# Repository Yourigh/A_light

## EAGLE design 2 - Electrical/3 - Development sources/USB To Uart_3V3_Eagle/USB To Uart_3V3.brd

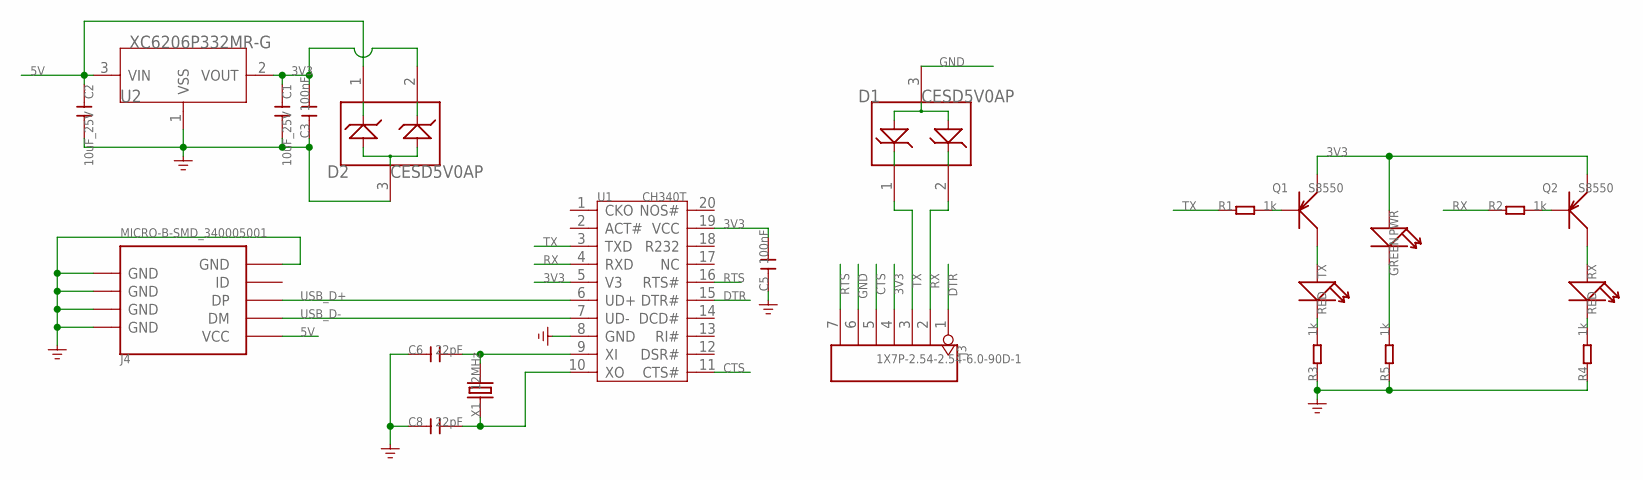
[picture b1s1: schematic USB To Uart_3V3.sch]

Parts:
C1, C2: 10uF_25V; C0805
C3, C5: 100nF; C0402
C6, C8: 22pF; C0402
D1, D2: CESD5V0AP; SOT23
J3: 1X7P-2.54-2.54-6.0-90D-1; 7P-2.54-65/35MIL
J4: MICRO-B-SMD_340005001; MICRO-USB
PWR: GREEN; LED-0603
Q1, Q2: S8550; SOT23
R1, R2, R3, R4, R5: 1k; R0402
RX: RED; LED-0603
TX: RED; LED-0603
U1: CH340T; SSOP20
U2: XC6206P332MR-G; SOT23
X1: 12MHz; HC49UP

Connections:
3V3: C1.1, C3.2, C5.2, D2.2, J3.4, PWR.+, Q1.2 (E), Q2.2 (E), U1.5 (V3), U1.19 (VCC), U2.2 (VOUT)
5V: C2.1, D2.1, J4.1 (VCC), U2.3 (VIN)
CTS: J3.5, U1.11 (CTS#)
DTR: J3.1, U1.15 (DTR#)
GND: C1.2, C2.2, C3.1, C5.1, C6.1, C8.1, D1.3, D2.3, J3.6, J4.5 (GND), J4.S1 (GND), J4.S2 (GND), J4.S3 (GND), J4.S4 (GND), J4.S5 (GND), J4.S6 (GND), R3.1, R4.1, R5.1, U1.8 (GND), U2.1 (VSS)
unnamed: Q1.3 (C), TX.+
unnamed: Q2.3 (C), RX.+
unnamed: C6.2, U1.9 (XI), X1.2
unnamed: C8.2, U1.10 (XO), X1.1
unnamed: R3.2, TX.-
unnamed: Q1.1 (B), R1.2
unnamed: Q2.1 (B), R2.2
unnamed: R4.2, RX.-
unnamed: PWR.-, R5.2
RTS: J3.7, U1.16 (RTS#)
RX: D1.2, J3.2, R2.1, U1.4 (RXD)
TX: D1.1, J3.3, R1.1, U1.3 (TXD)
USB_D+: J4.3 (DP), U1.6 (UD+)
USB_D-: J4.2 (DM), U1.7 (UD-)

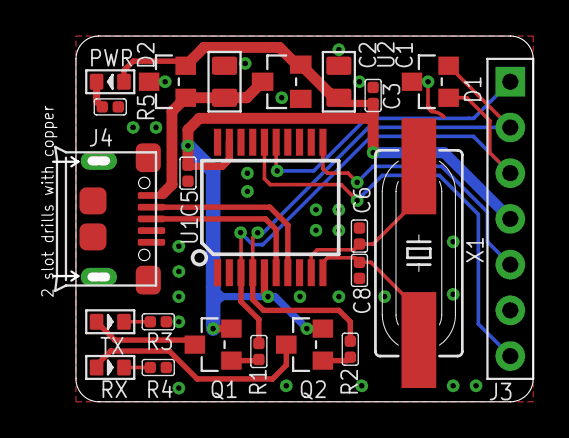
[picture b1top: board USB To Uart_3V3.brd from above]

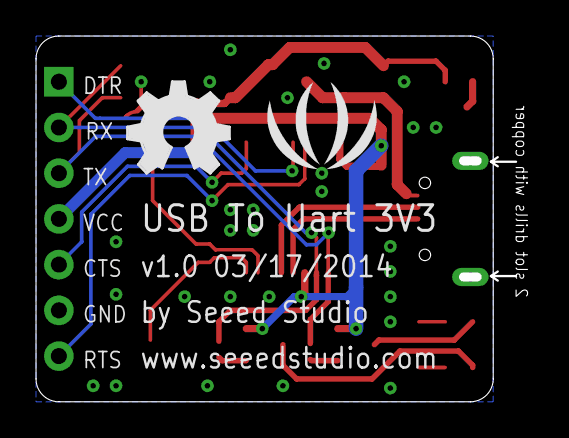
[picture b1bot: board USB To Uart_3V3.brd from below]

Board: 2 copper layers, 26.7 x 20.3 mm, 25 parts (2 on the bottom side), 19 nets.

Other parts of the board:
U$8: LOGO_SILK
U$9: OSHW_FILLX200_NOTEXT

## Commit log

2020-11-07 add code
2020-11-07 MQTT connected
    connected to broker, broker reported
    1604775397: New client connected from 192.168.1.8 as A-light (p2, c1, k15, u'homeassistant').
    1604775420: Client A-light has exceeded timeout, disconnecting.
2020-11-07 MQTT identified by chip ID
2020-11-07 publighing and subsc
    Publishing works, subcribing not tested.
    Abandoned work, because RF remote connected control is limited (not knowing the state, cannot guarantee ON or OFF state on demand).
2020-11-07 increased delay on mDNS reponder
    less fails on boot
2020-12-22 usong ntp clinet
2020-12-22 bug fix RTC error report
2020-12-22 NTP works, no summer time, menu begin.
2020-12-22 added summer time with EEPROm seving
2020-12-22 changed reset behaviour
2025-09-19 fix http client, to be able to build. not tested
2025-09-20 chnage dark mode
2025-09-22 night mode edit - middle LED on.
2025-10-06 reconnect in gradually increasing intervals if wifi lost, AP after 1h40m
2025-10-06 dimmer animnation
2026-06-05 Improve WiFi reconnect recovery
